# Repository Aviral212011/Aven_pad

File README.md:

# AVENPAD – Custom Macropad

AVENPAD is a compact, custom-designed macropad built for productivity, creativity, and everyday convenience. It features a minimal yet powerful layout with 5 mechanical switches and a rotary encoder which is making it perfect for shortcuts and media control .

---

##  Features of AVENPAD
* 5 Programmable Mechanical Switches that can be used to assign any shotcut or custom action to each key .

* Rotary Encoder can be used for volume adjustment , scrolling or any custom function .
  
* I used XIAO RP2040 microcontroller which is Compact and powerful microcontroller based on the RP2040 chip.

* the PCB of AVENPAD is designed in Kicad and the case is designed in onshape .

---
##   Images 
* pcb
  
* schematics
  
* pcb 3d view
  
* case

---
## Hardware Used-

* [Seeed Studio XIAO RP2040](https://wiki.seeedstudio.com/XIAO-RP2040/)
* 5x Mechanical Switches
* 1x Rotary Encoder
* Custom PCB
* 3D Printed Case

---

## Why did I make it?
* I always keep forgetting windows shotcuts and I really needed a quick way to switch between windows without having using the shotcuts that's why i designed the AVENPAD.

---
## Onshape link -
* https://cad.onshape.com/documents/871017228e423d2eaa0219d3/w/cf6216e0fa05433caa6062cb/e/ab9a9642b0b903e0340806be?renderMode=0&uiState=69c7d780b2c31718861df9a4
---

## Author

**Aviral Sen**

> AVENPAD is a simple yet powerful tool to enhance your digital workflow and productivity.

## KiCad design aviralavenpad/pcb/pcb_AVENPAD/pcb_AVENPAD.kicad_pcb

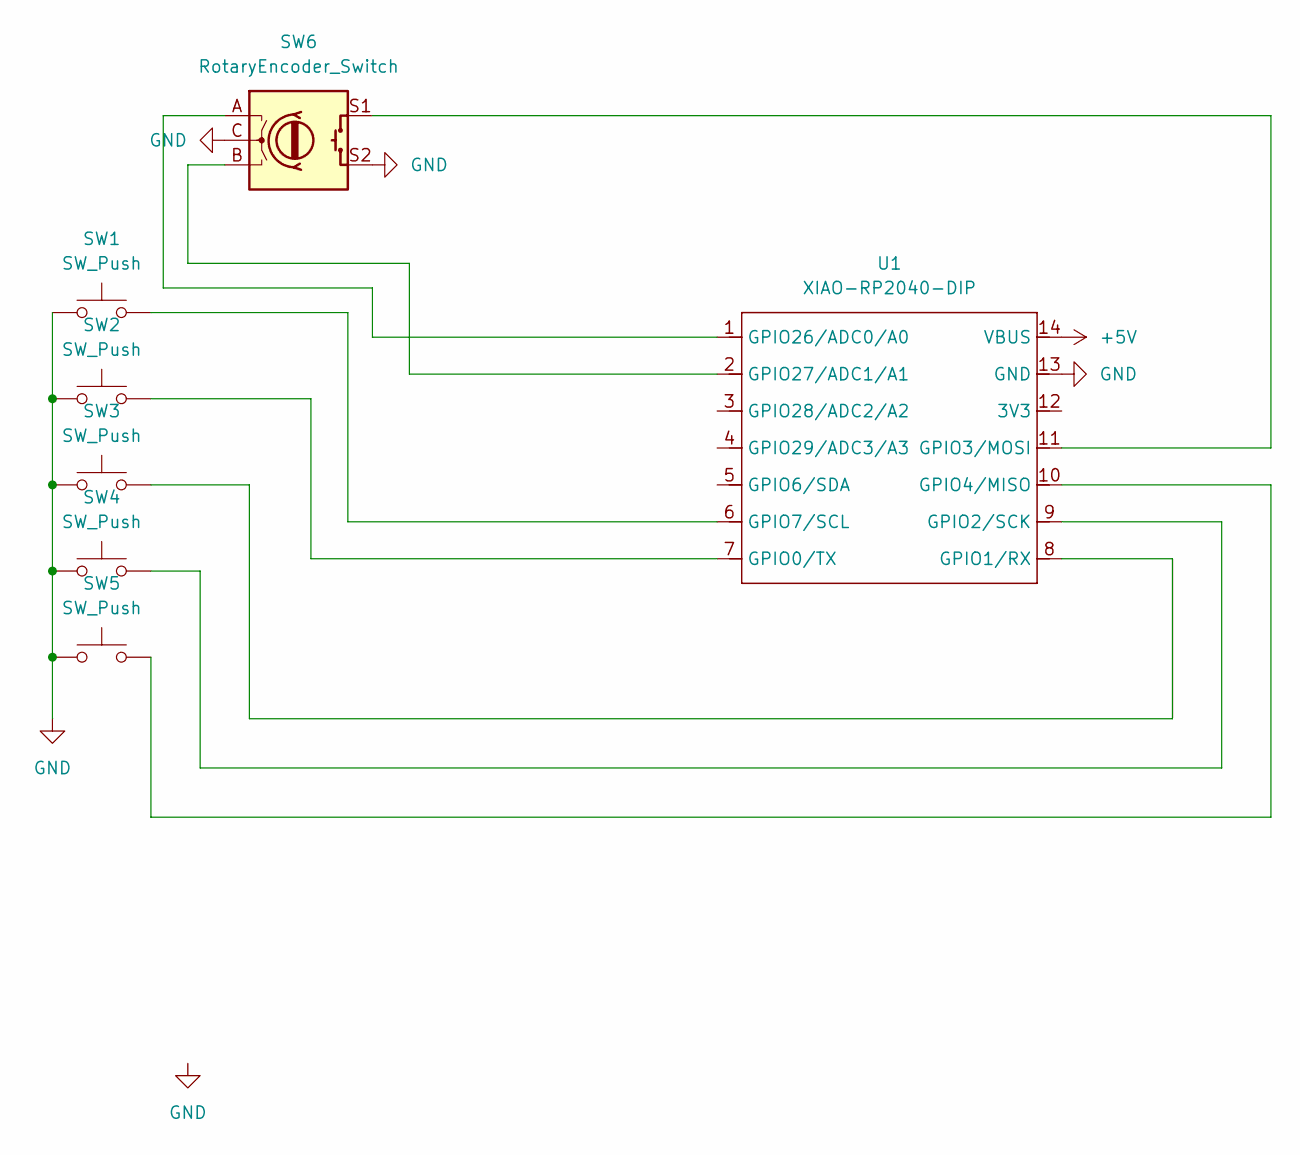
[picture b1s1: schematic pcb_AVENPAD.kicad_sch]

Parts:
SW1, SW2, SW3, SW4, SW5: SW_Push; SW_Cherry_MX_1.00u_PCB
SW6: RotaryEncoder_Switch; RotaryEncoder_Alps_EC11E-Switch_Vertical_H20mm
U1: XIAO-RP2040-DIP; MCU_Seeed_ESP32C3

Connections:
+5V: U1.14 (VBUS)
GND: SW1.1, SW2.1, SW3.1, SW4.1, SW5.1, SW6.C, SW6.S2, U1.13 (GND)
unnamed: SW2.2, U1.7 (GPIO0/TX)
unnamed: SW3.2, U1.8 (GPIO1/RX)
unnamed: SW4.2, U1.9 (GPIO2/SCK)
unnamed: SW6.S1, U1.11 (GPIO3/MOSI)
unnamed: SW5.2, U1.10 (GPIO4/MISO)
unnamed: SW1.2, U1.6 (GPIO7/SCL)
unnamed: SW6.A, U1.1 (GPIO26/ADC0/A0)
unnamed: SW6.B, U1.2 (GPIO27/ADC1/A1)

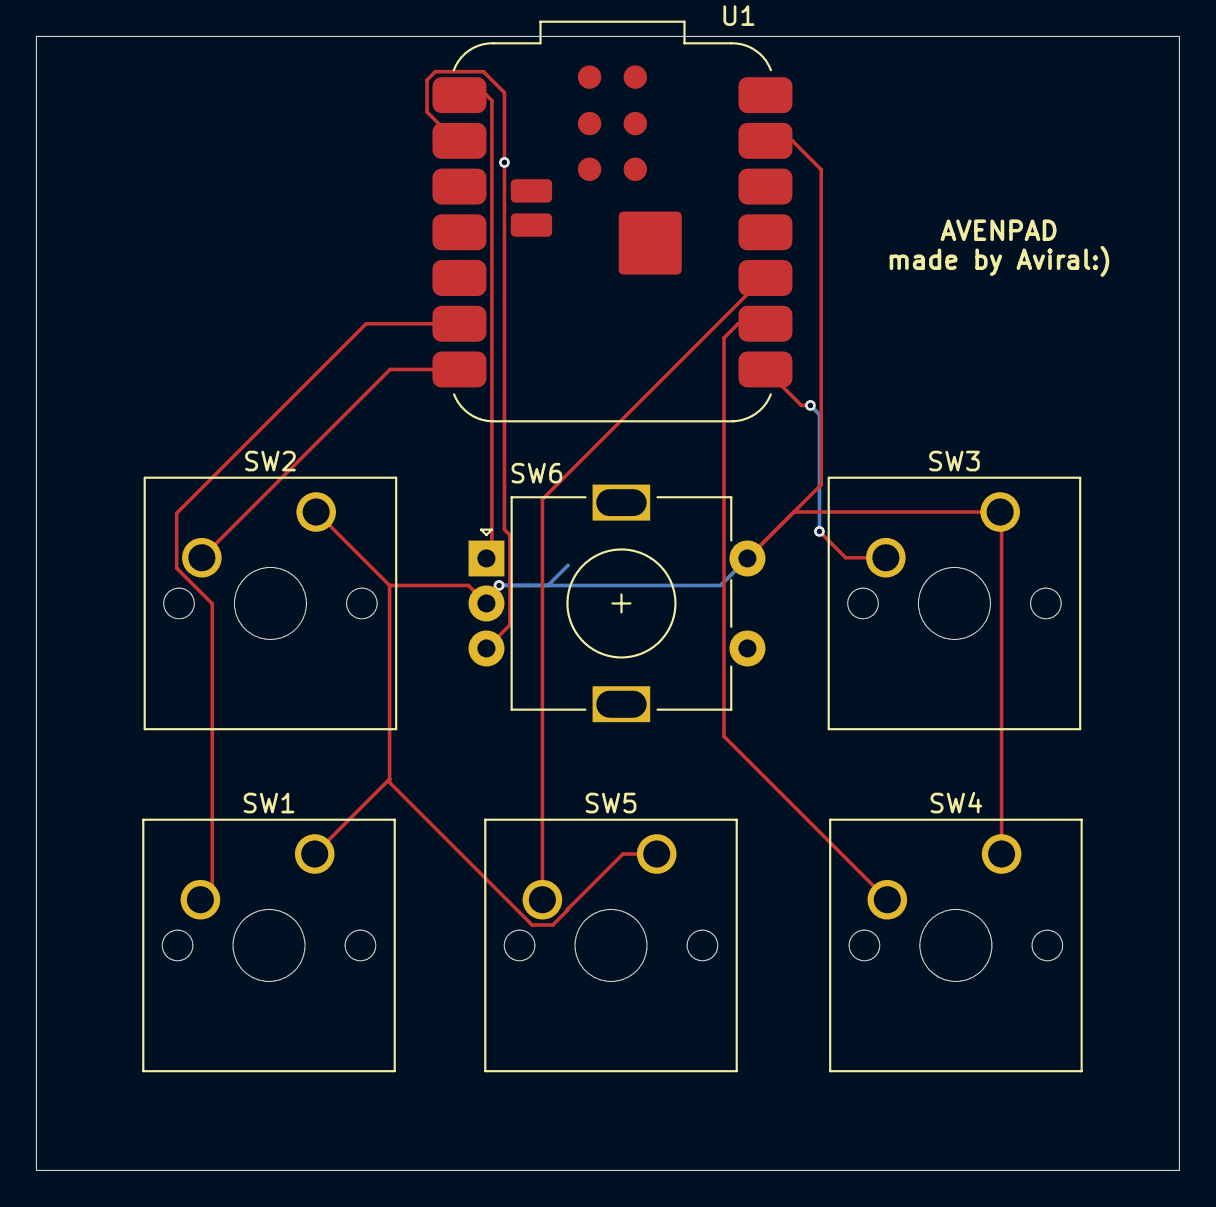
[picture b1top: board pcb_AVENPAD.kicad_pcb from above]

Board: 2 copper layers, 63.5 x 63.0 mm, 7 parts (0 on the bottom side), 9 nets.

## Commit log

2026-03-25 Update hardware list with link for XIAO RP2040
